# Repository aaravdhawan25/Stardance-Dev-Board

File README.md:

# AD Dev Pad

This is the **AD Dev Pad**, a custom 6-key mechanical macropad I designed and built from scratch to make my coding workflow way faster. I was getting tired of clicking through menus just to mute Discord or push my code, so I made this board to handle all my repetitive tasks. 

## Features
I programmed this specifically for a Mac developer environment. It handles a lot more than just typing basic shortcuts!

* **Smart Discord Mute:** The top-left button does the `Cmd + Shift + M` shortcut to toggle mute. But the coolest part is that the Python code actually tracks the state, so when I'm muted, the entire board's underglow turns **RED** as a indicator. When I unmute, it goes back to my default which is **GREEN**.
* **No Mouse Github Commands:** I have dedicated keys that launch Mac Spotlight, type "github desktop", wait for it to load, and hit enter. Another key runs a full sequence to auto-commit, and another instantly pushes the code.
  
* **Basic Necessity stuff:** Easy keys to Copy (`Cmd + C`), Paste (`Cmd + V`), and Undo (`Cmd + Z`).

## Hardware and PCB
I designed the board myself using KiCad. I wanted it to be simple but look really clean, so I added some custom silkscreen graphics on the front and back that mix my initials (AD) with a GitHub cat because it's cool.

### Parts List
* **Microcontroller:** Seeed Studio XIAO. It is super tiny but has exactly enough pins for this project.
* **Switches:** 6 standard mechanical keyboard switches. 
* **Wiring:** I used a "direct-to-pin" setup. Every single switch gets its own dedicated pin on the XIAO and pulls straight to Ground. No complicated matrix or diodes needed!
* **RGB LEDs:** 6 `SK6812MINI-E` reverse-mount LEDs. They are soldered onto the bottom of the board and shine *up* through cutouts in the PCB directly into the bottom of the switches.

## Firmware
I didn't want to mess with compiling complicated C code, so this board runs on **KMK**. 

The XIAO literally just shows up on my computer like a USB flash drive. If I want to change a macro, I just open `code.py` in a text editor, change the shortcut, and hit save. Then It updates instantly. 

*Note for anyone building this: The LEDs are powered directly from the XIAO's `3V3` pin. Because that pin can only handle about 200mA before the board gets too hot, I capped the RGB brightness (`val_limit=100`) in the code to keep everything safe!*

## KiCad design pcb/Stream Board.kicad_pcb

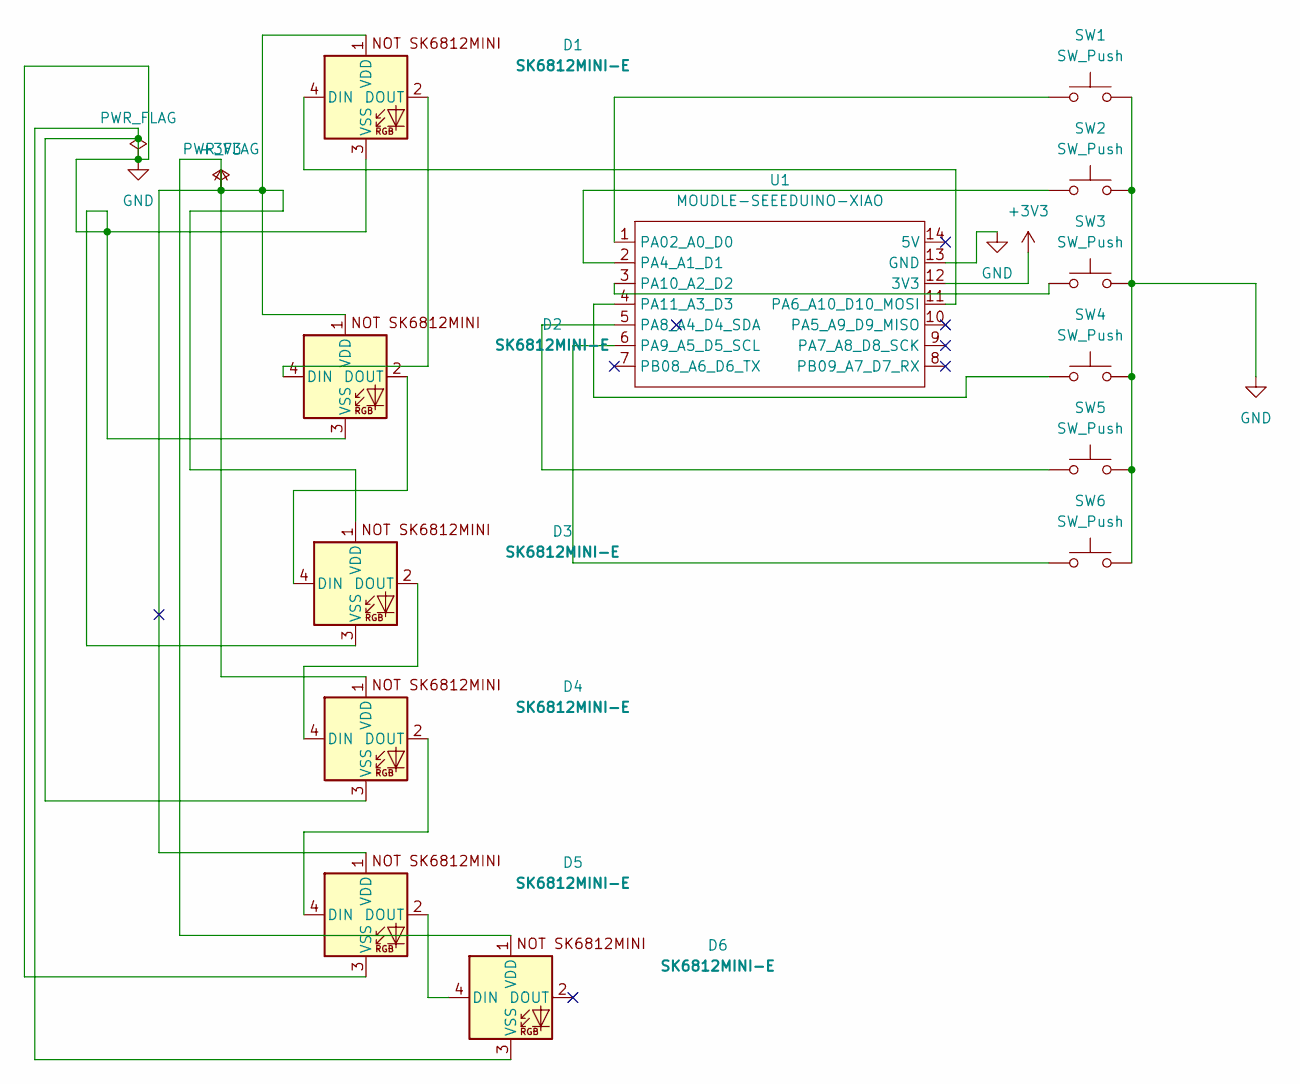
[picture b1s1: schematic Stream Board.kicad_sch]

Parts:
D1, D2, D3, D4, D5, D6: SK6812MINI-E; SK6812MINI-E_fixed
SW1, SW2, SW3, SW4, SW5, SW6: SW_Push; SW_Cherry_MX_1.00u_PCB
U1: MOUDLE-SEEEDUINO-XIAO; XIAO-Generic-Hybrid-14P-2.54-21X17.8MM

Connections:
+3V3: D1.1 (VDD), D2.1 (VDD), D3.1 (VDD), D4.1 (VDD), D5.1 (VDD), D6.1 (VDD), U1.12 (3V3)
GND: D1.3 (VSS), D2.3 (VSS), D3.3 (VSS), D4.3 (VSS), D5.3 (VSS), D6.3 (VSS), SW1.2, SW2.2, SW3.2, SW4.2, SW5.2, SW6.2, U1.13 (GND)
unnamed: D1.4 (DIN), U1.11 (PA6_A10_D10_MOSI)
unnamed: D1.2 (DOUT), D2.4 (DIN)
unnamed: D2.2 (DOUT), D3.4 (DIN)
unnamed: D3.2 (DOUT), D4.4 (DIN)
unnamed: D4.2 (DOUT), D5.4 (DIN)
unnamed: D5.2 (DOUT), D6.4 (DIN)
unnamed: SW1.1, U1.1 (PA02_A0_D0)
unnamed: SW2.1, U1.2 (PA4_A1_D1)
unnamed: SW5.1, U1.5 (PA8_A4_D4_SDA)
unnamed: SW6.1, U1.6 (PA9_A5_D5_SCL)
unnamed: SW3.1, U1.3 (PA10_A2_D2)
unnamed: SW4.1, U1.4 (PA11_A3_D3)

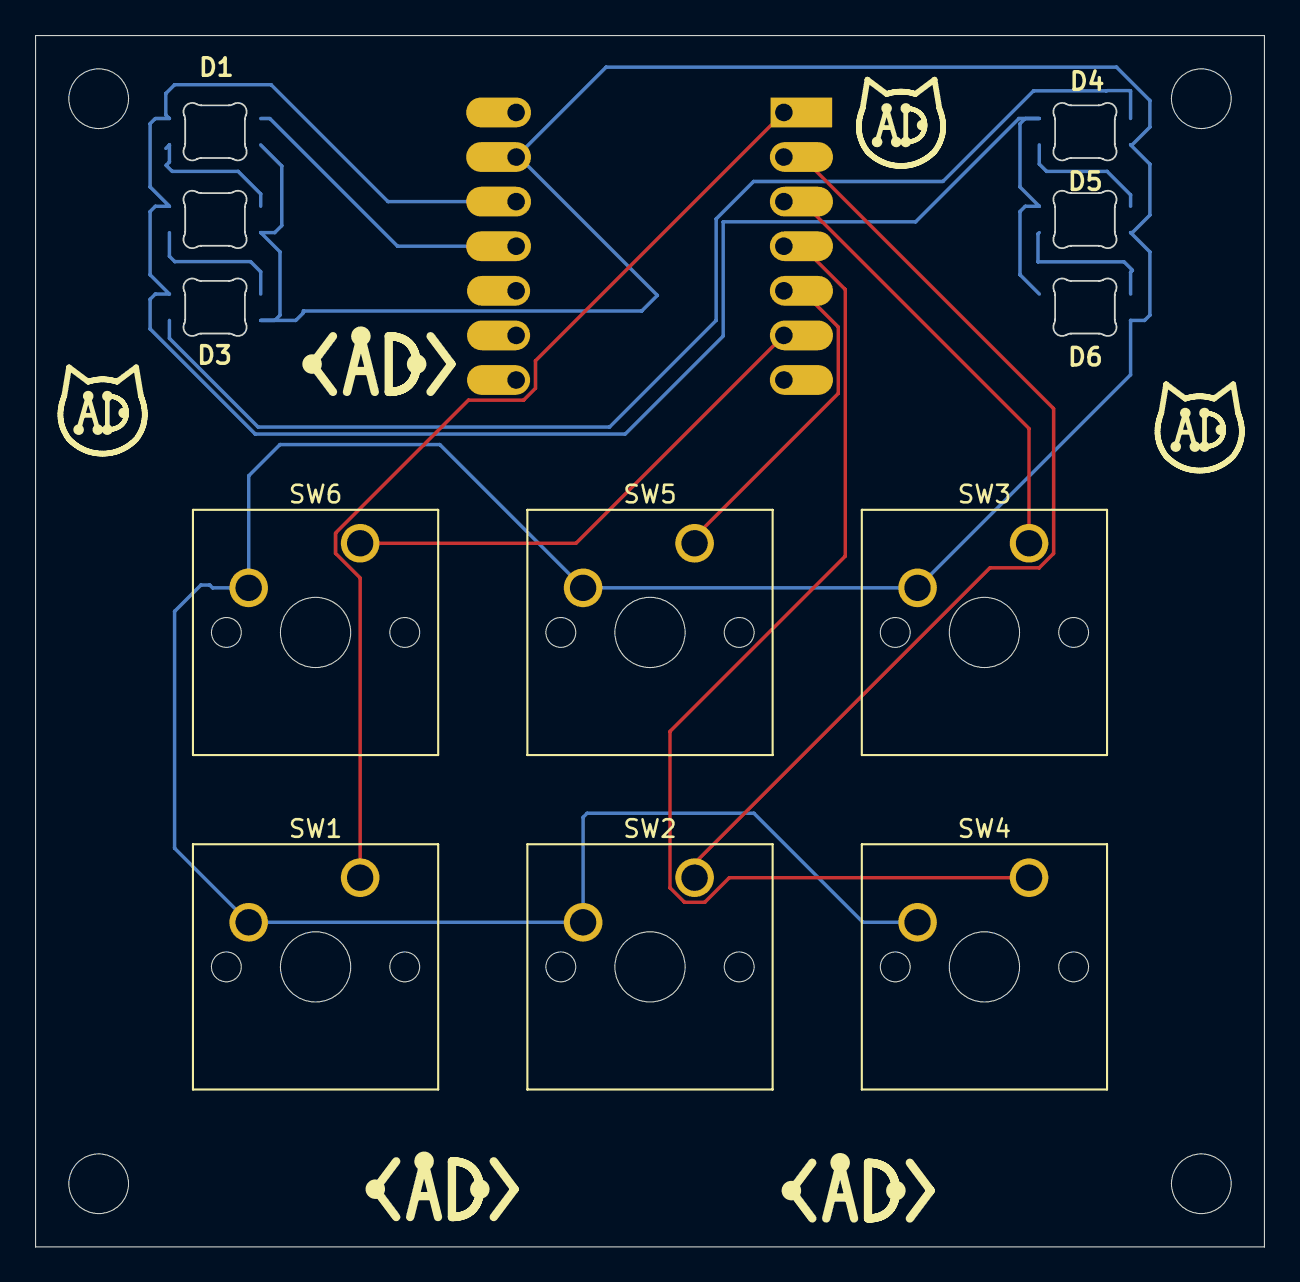
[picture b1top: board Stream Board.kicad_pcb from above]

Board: 2 copper layers, 69.9 x 69.0 mm, 13 parts (1 on the bottom side), 14 nets.

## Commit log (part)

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2026-06-19 Revise README for Stardance Dev Board details
    Updated the README to reflect the new Stardance Dev Board features, specifications, and setup instructions.
2026-06-19 Change project title to 'Stardance Dev Board'
    Updated the project title in the README.
2026-06-19 Add PCB FIles
2026-06-19 refactor
2026-06-19 Add KMK firmware for custom keyboard
    Introduce a new KMK-based firmware (Firmware/firm.py) that configures the keyboard matrix pins, RGB LEDs, and macros. Adds RGB extension with defaults, a Macros module, app-launching macros (GitHub D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
2026-06-19 replace all files to correct
2026-06-19 Add .DS_Store files; rename production zip
    Adds macOS .DS_Store metadata files at the repository root and in 'Production Files'. Renames 'Production Files/GerberFIles.zip' to 'Production Files/ProductionFiles.zip' (binary contents changed; si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
